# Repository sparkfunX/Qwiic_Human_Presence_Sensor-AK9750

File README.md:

Qwiic Human Presence Sensor - AK9750
========================================

[*SPX-14289*](https://www.sparkfun.com/products/14289)

The AK9750 is a passive infrared sensor with four discrete sensors built into one digital package. PIRs are most often used in security systems to detect the movement of a human talking through the room. If you've ever seen a 1" white sphere in the corner of a room, that's a PIR. We sell a [simple PIR](https://www.sparkfun.com/products/13285) as well. The problem with PIRs is many fold. The vast majority of PIRs use a simple on/off interface. The AK9750 is a digital sensor giving you a 16-bit digital value over I<sup>2</sup>C. Furthermore, the AK9750 has *four* sensors built in! This allows you to detect not only presence but relative distance and direction of movement (for example: PIR2 went off then PIR4 went off so the human is moving left to right).

Each of the four sensors outputs the IR current in pico-amps (-14,286 to 14,286pA). A PIR reading can vary from roughly -200 (no human present) to 1500 when a human is detected standing in front of a given channel but it varies due to environmental factors and other heat sources in view. We've written a library to control the sensor and included a examples showing how to output the sensor readings. We've also written a Processing sketch to visualize the IR sensor readings in real time. 

The Qwiic Human Presence Sensor - AK9750 is rear mounted through the 0.8mm thick PCB. Additionally, the sensor ships without a lens. We've found the sensor to perform quite well and detect human movement over 10 feet (3 meters) away without the standard Fresnel lens. 

Need many eyes in the sky? The ADR jumpers allow up to 3 sensors on a bus. Need more? Our [Qwiic Mux](https://www.sparkfun.com/products/14257) will enable up to 192 sensors for a total of 768 presence readings. Eeek!

This board includes Qwiic connectors. The [Qwiic system](http://www.sparkfun.com/qwiic) enables fast and solderless connection between popular platforms and various sensors and actuators. You can read more about the Qwiic system [here](http://www.sparkfun.com/qwiic).

Repository Contents
-------------------

* **/Documents** - AK9750 datasheet and graph of movement detection. 
* **/Firmware** - Example sketches for the library (.ino). Run these from the Arduino IDE. 
* **/Hardware** - Source files for the PCB layout in EAGLE (.brd, .sch).
* **/Visualizer** - Processing sketch with matching Arduino sketch to see data on a heat map.

License Information
-------------------

This product is _**open source**_!

Please review the LICENSE.md file for license information.

If you have any questions or concerns on licensing, please contact techsupport@sparkfun.com.

Distributed as-is; no warranty is given.

- Your friends at SparkFun.

_<COLLABORATION CREDIT>_

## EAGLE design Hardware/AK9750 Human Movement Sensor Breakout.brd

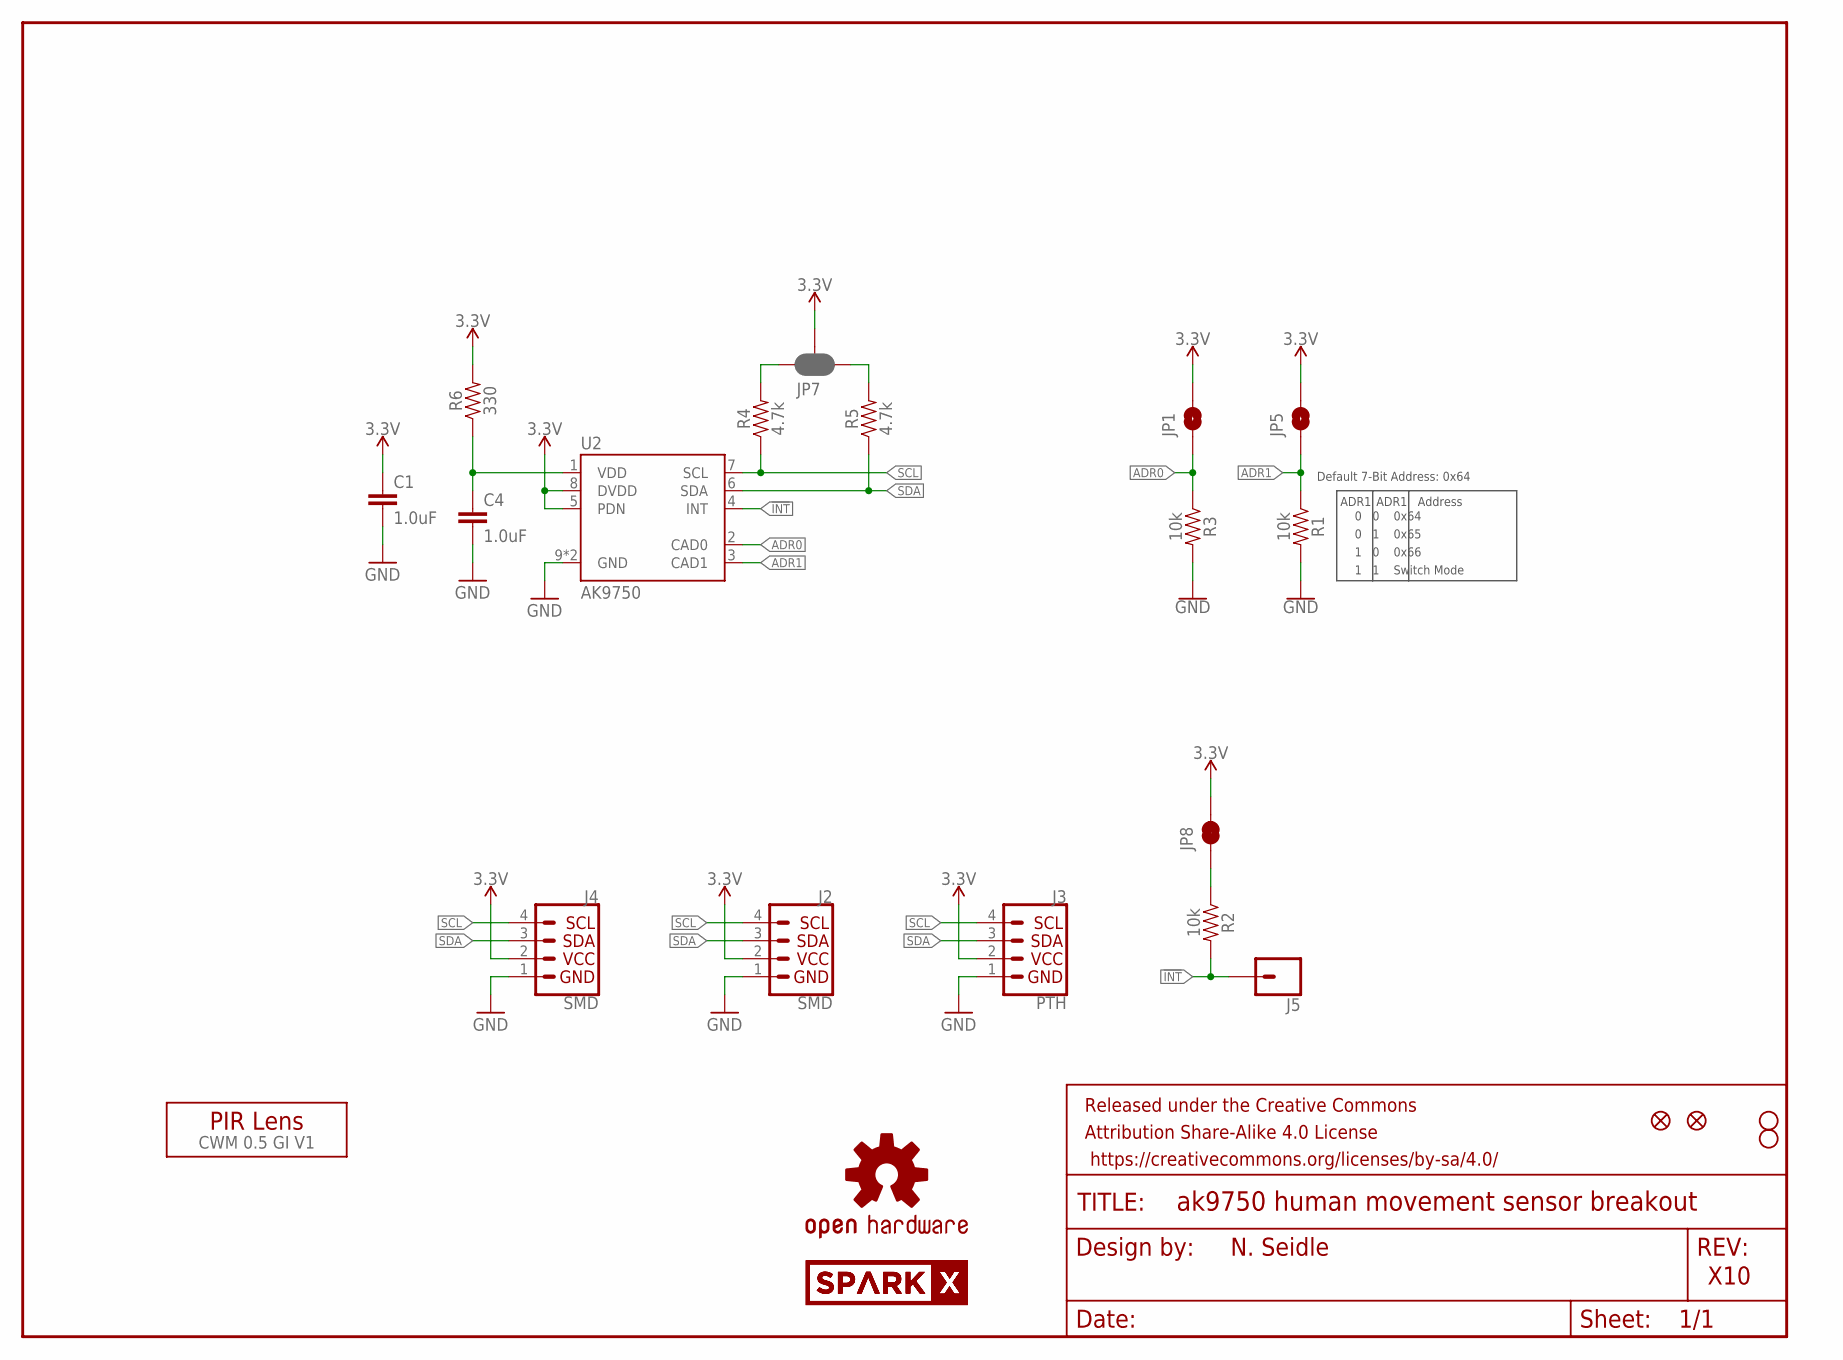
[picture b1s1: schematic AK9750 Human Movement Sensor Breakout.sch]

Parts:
C1, C4: 1.0uF; 0603
FRAME1: FRAME-LETTER; CREATIVE_COMMONS
J2, J4: SMD; 1X04_1MM_RA
J3: PTH; 1X04_NO_SILK
J5: CONN_01PTH_NO_SILK_YES_STOP; 1X01_NO_SILK
JP1, JP5: JUMPER-SMT_2_NO_SILK; SMT-JUMPER_2_NO_SILK
JP2, JP6: FIDUCIALUFIDUCIAL; MICRO-FIDUCIAL
JP3, JP4: STAND-OFF
JP7: JUMPER-SMT_3_2-NC_PASTE_SILK; SMT-JUMPER_3_2-NC_PASTE_SILK
JP8: JUMPER-SMT_2_NC_TRACE_SILK; SMT-JUMPER_2_NC_TRACE_SILK
LOGO1: OSHW-LOGOMINI; OSHW-LOGO-MINI
R1, R2, R3: 10k; 0603
R4, R5: 4.7k; 0603
R6: 330; 0603
U2: AK9750; SON10
U$1, U$2: SPARKX-LOGO4; SPARKX-MEDIUM
U$3: CWM 0.5 GI V1; LENS-CWM-0.5-GI-V1

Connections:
3.3V: C1.1, J2.2 (VCC), J3.2 (VCC), J4.2 (VCC), JP1.2, JP5.2, JP7.2, JP8.2, R6.2, U2.5 (PDN), U2.8 (DVDD)
!INT: J5.1, R2.2, U2.4 (INT)
ADR0: JP1.1, R3.1, U2.2 (CAD0)
ADR1: JP5.1, R1.1, U2.3 (CAD1)
GND: C1.2, C4.2, J2.1 (GND), J3.1 (GND), J4.1 (GND), R1.2, R3.2, U2.9 (GND), U2.10 (GND)
unnamed: JP7.1, R5.2
unnamed: JP7.3, R4.2
unnamed: JP8.1, R2.1
SCL: J2.4 (SCL), J3.4 (SCL), J4.4 (SCL), R4.1, U2.7 (SCL)
SDA: J2.3 (SDA), J3.3 (SDA), J4.3 (SDA), R5.1, U2.6 (SDA)
VDD: C4.1, R6.1, U2.1 (VDD)

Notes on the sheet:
N. Seidle
X10
Default 7-Bit Address: 0x64
ADR1
0 0 0x64
Address
0 1 0x65
1 0 0x66
1 1 Switch Mode

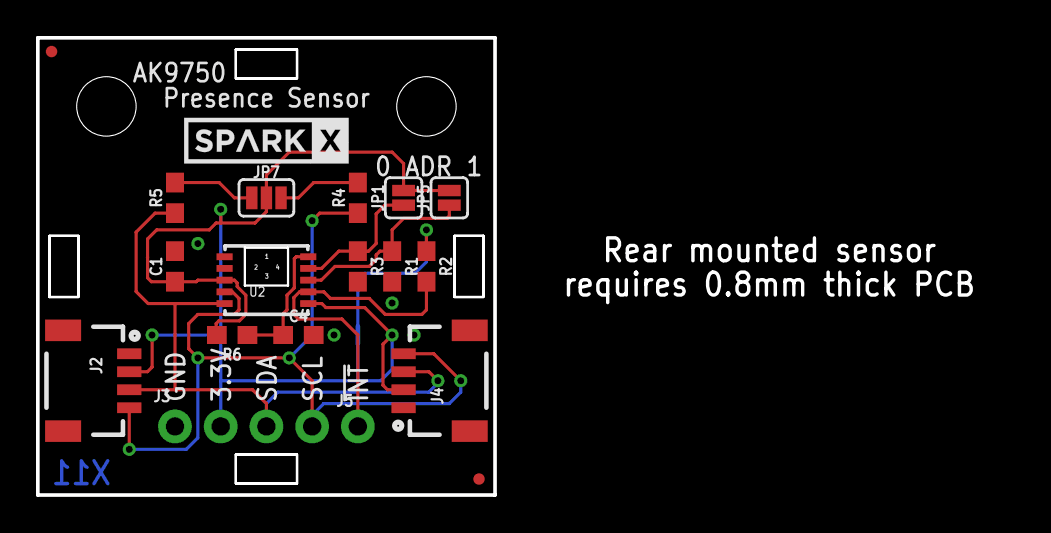
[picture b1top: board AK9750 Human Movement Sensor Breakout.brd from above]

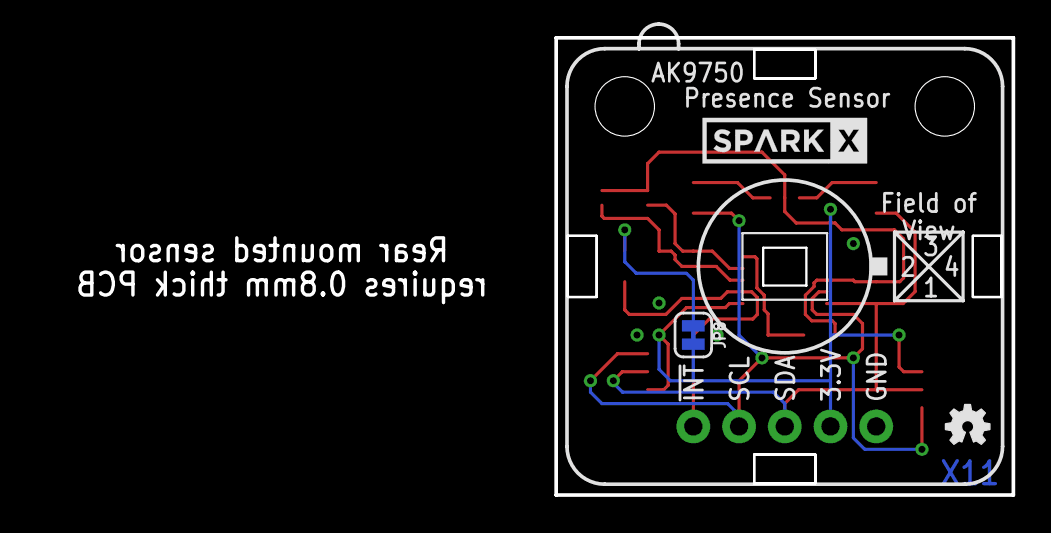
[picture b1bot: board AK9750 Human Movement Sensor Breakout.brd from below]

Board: 2 copper layers, 54.2 x 25.4 mm, 26 parts (4 on the bottom side), 11 nets.

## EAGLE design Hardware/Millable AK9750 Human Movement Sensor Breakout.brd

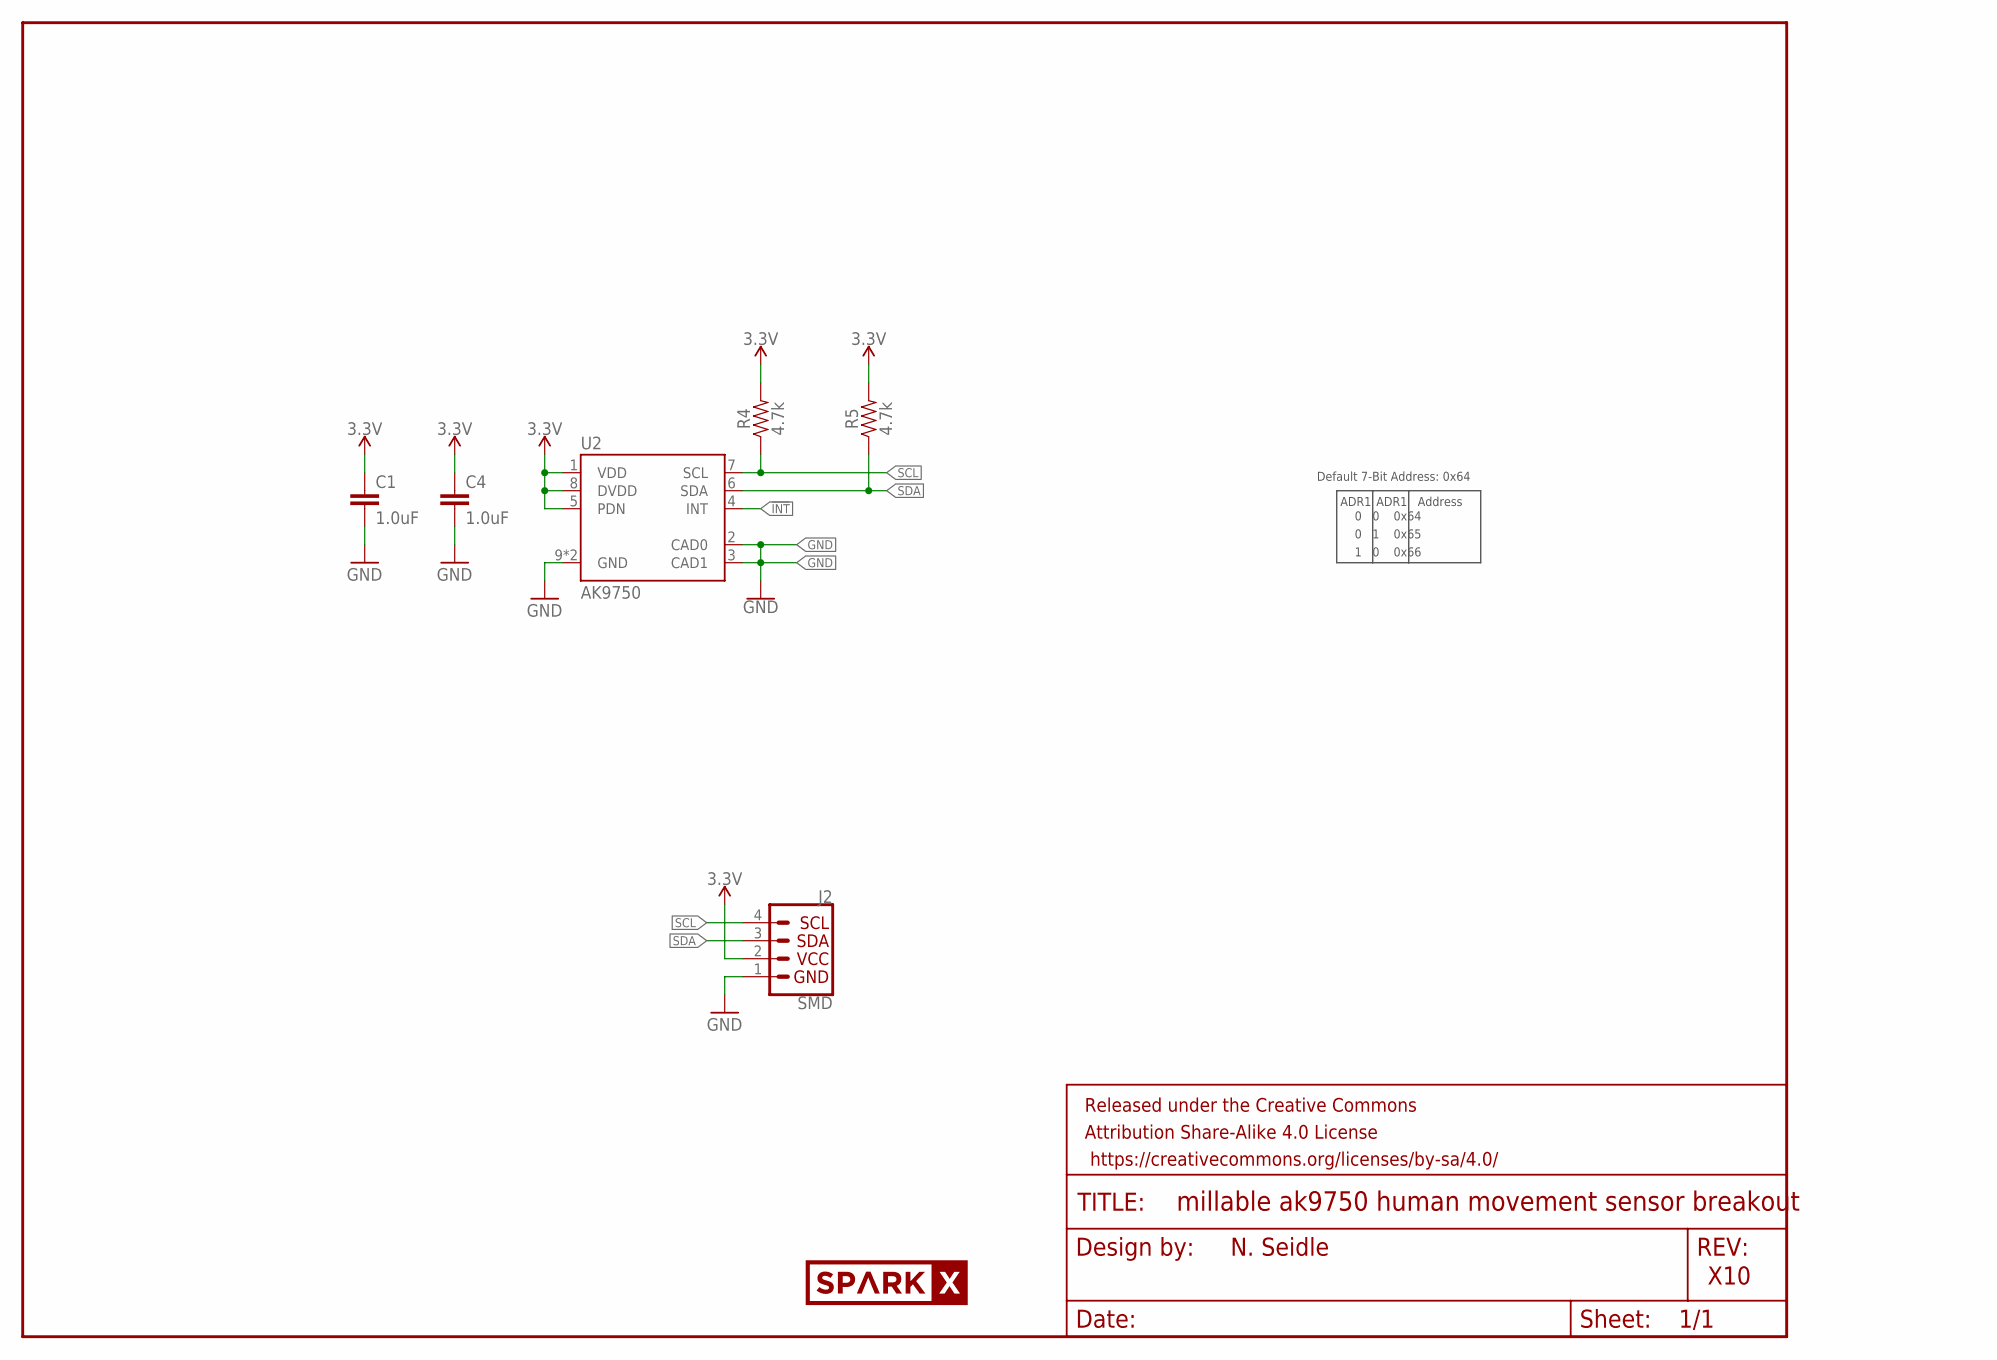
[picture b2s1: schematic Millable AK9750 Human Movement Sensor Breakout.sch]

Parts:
C1, C4: 1.0uF; 0603
FRAME1: FRAME-LETTER; CREATIVE_COMMONS
J2: SMD; 1X04_1MM_RA
R4, R5: 4.7k; 0603
U2: AK9750; SON10
U$2: SPARKX-LOGO4; SPARKX-MEDIUM

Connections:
3.3V: C1.1, C4.1, J2.2 (VCC), R4.2, R5.2, U2.1 (VDD), U2.5 (PDN), U2.8 (DVDD)
!INT: U2.4 (INT)
GND: C1.2, C4.2, J2.1 (GND), U2.2 (CAD0), U2.3 (CAD1), U2.9 (GND), U2.10 (GND)
SCL: J2.4 (SCL), R4.1, U2.7 (SCL)
SDA: J2.3 (SDA), R5.1, U2.6 (SDA)

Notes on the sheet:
N. Seidle
X10
Default 7-Bit Address: 0x64
ADR1
0 0 0x64
Address
0 1 0x65
1 0 0x66

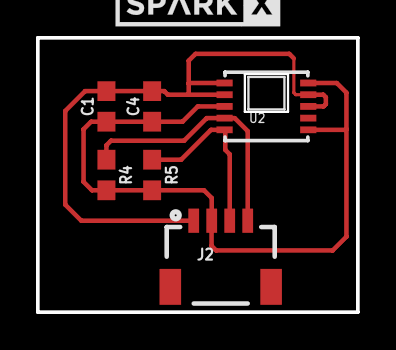
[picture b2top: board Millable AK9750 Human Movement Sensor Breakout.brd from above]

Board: 2 copper layers, 17.8 x 15.2 mm, 8 parts (0 on the bottom side), 4 nets.

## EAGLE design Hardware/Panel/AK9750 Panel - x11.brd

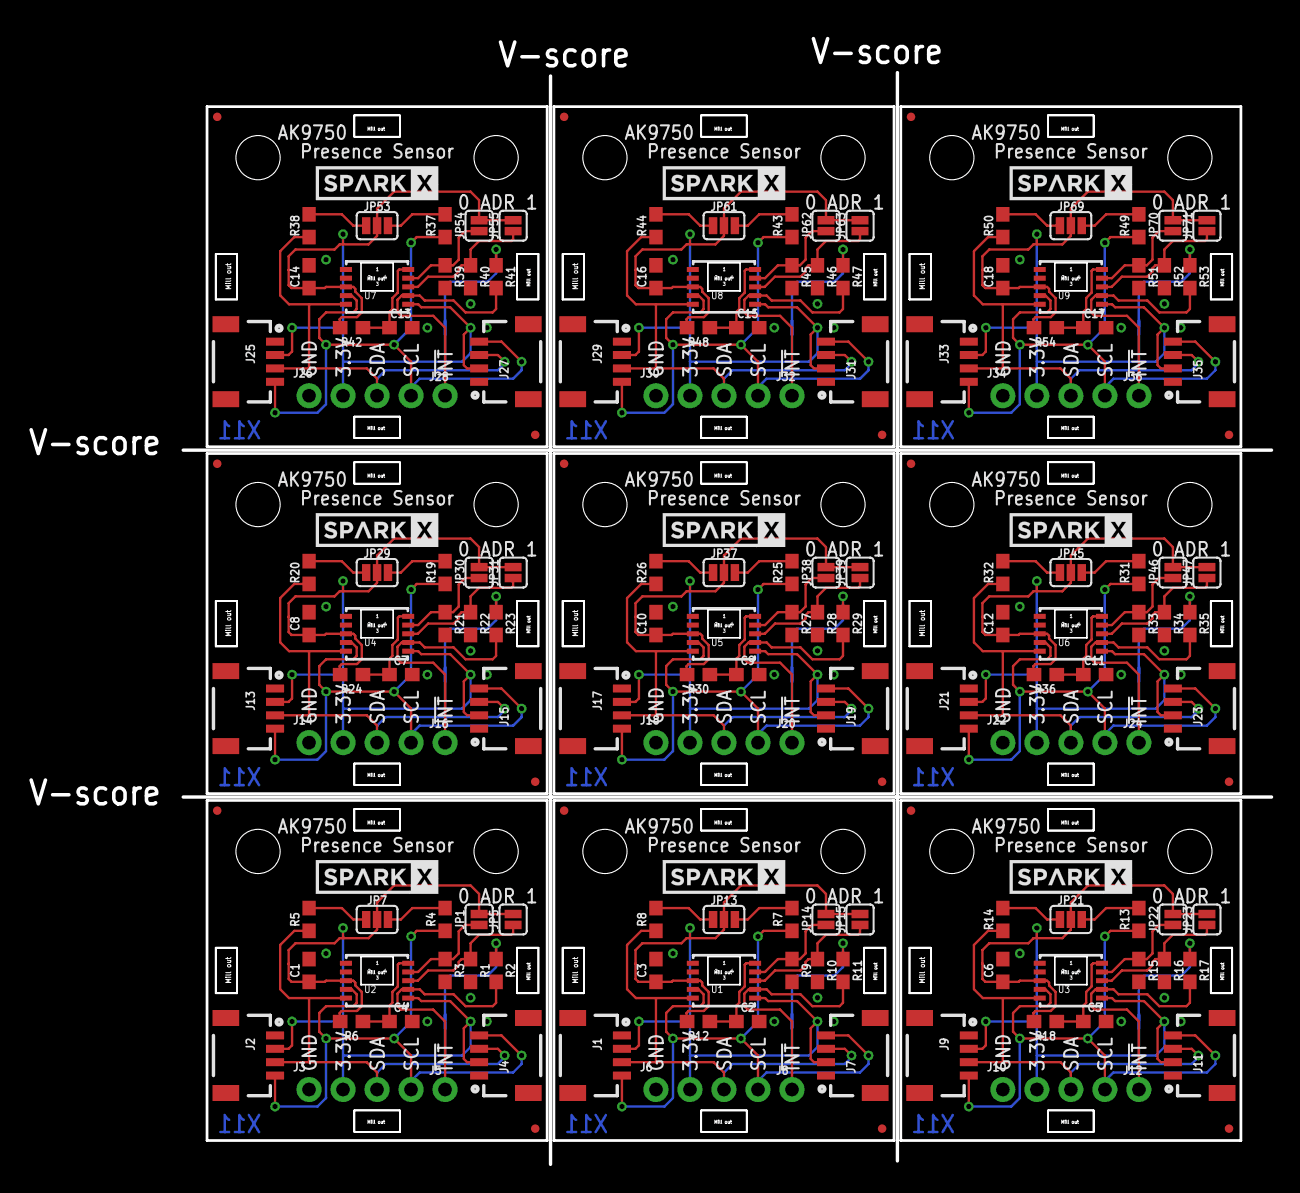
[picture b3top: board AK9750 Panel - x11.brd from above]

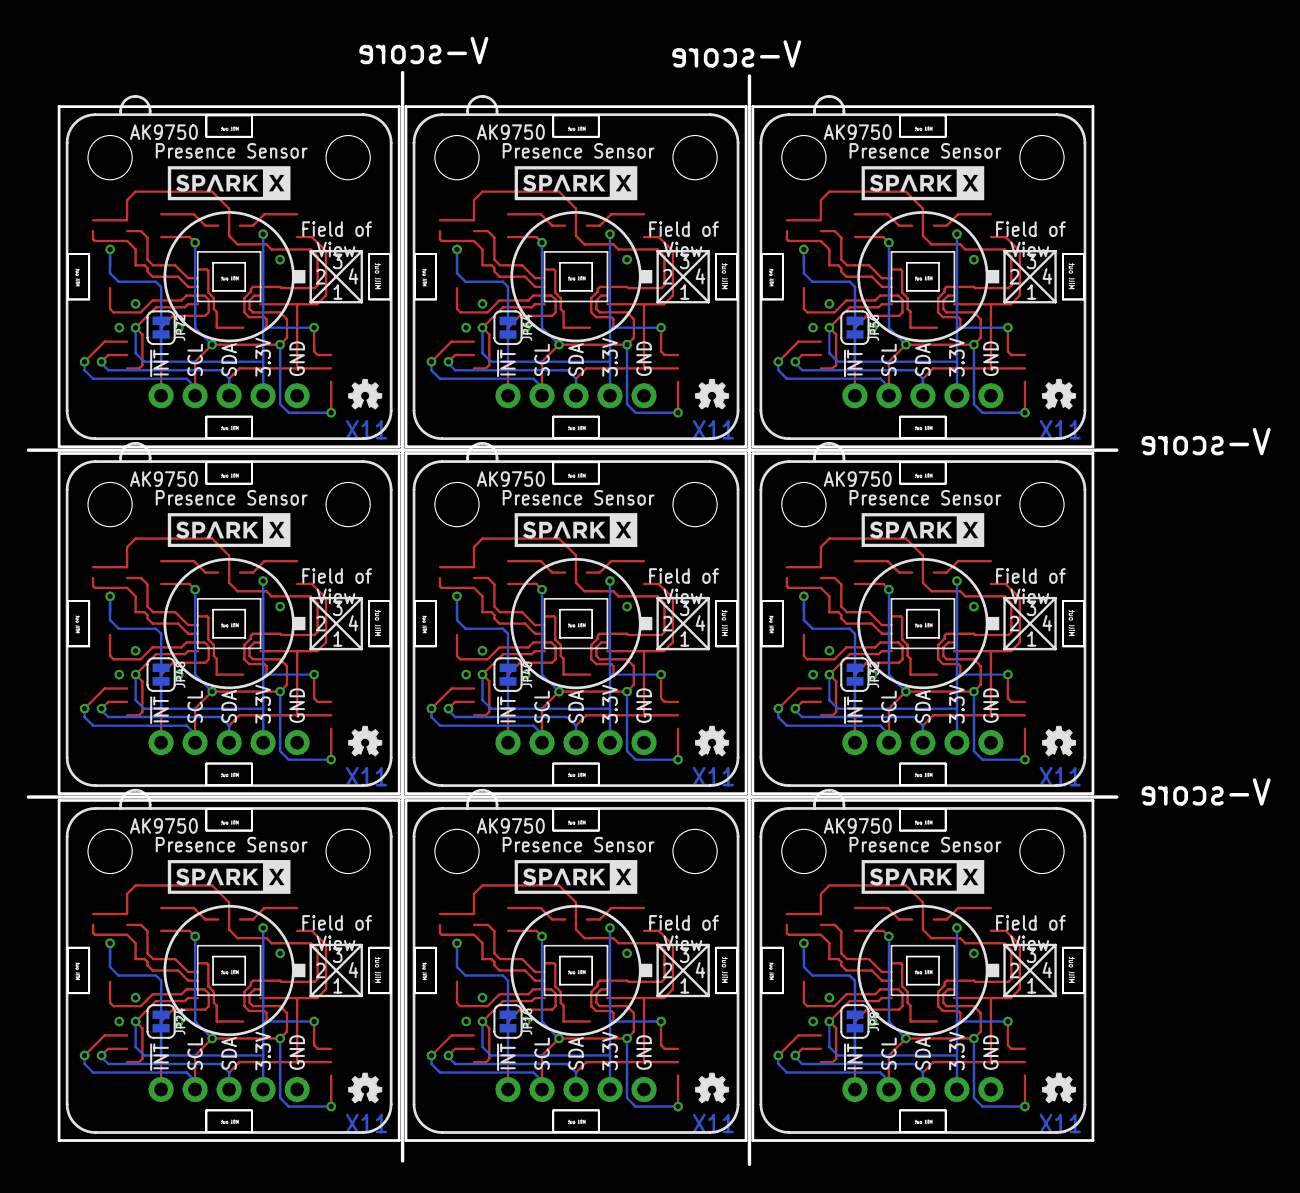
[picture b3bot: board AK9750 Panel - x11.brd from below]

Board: 2 copper layers, 92.8 x 84.8 mm, 225 parts (36 on the bottom side), 99 nets.

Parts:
C1, C2, C3, C4, C5, C6, C7, C8, C9, C10, C11, C12, C13, C14, C15, C16, C17, C18: 1.0uF; 0603
J1, J2, J4, J7, J9, J11, J13, J15, J17, J19, J21, J23, J25, J27, J29, J31, J33, J35: SMD; 1X04_1MM_RA
J3, J6, J10, J14, J18, J22, J26, J30, J34: PTH; 1X04_NO_SILK
J5, J8, J12, J16, J20, J24, J28, J32, J36: 1X01_NO_SILK
JP1, JP5, JP14, JP15, JP22, JP23, JP30, JP31, JP38, JP39, JP46, JP47, JP54, JP55, JP62, JP63, JP70, JP71: SMT-JUMPER_2_NO_SILK
JP2, JP6, JP11, JP12, JP19, JP20, JP27, JP28, JP35, JP36, JP43, JP44, JP51, JP52, JP59, JP60, JP67, JP68: FIDUCIALUFIDUCIAL; MICRO-FIDUCIAL
JP3, JP4, JP9, JP10, JP17, JP18, JP25, JP26, JP33, JP34, JP41, JP42, JP49, JP50, JP57, JP58, JP65, JP66: STAND-OFF
JP7, JP13, JP21, JP29, JP37, JP45, JP53, JP61, JP69: SMT-JUMPER_3_2-NC_PASTE_SILK
JP8, JP16, JP24, JP32, JP40, JP48, JP56, JP64, JP72: SMT-JUMPER_2_NC_TRACE_SILK
LOGO1, LOGO2, LOGO3, LOGO4, LOGO5, LOGO6, LOGO7, LOGO8, LOGO9: OSHW-LOGOMINI; OSHW-LOGO-MINI
R1, R2, R3, R9, R10, R11, R15, R16, R17, R21, R22, R23, R27, R28, R29, R33, R34, R35, R39, R40, R41, R45, R46, R47, R51, R52, R53: 10k; 0603
R4, R5, R7, R8, R13, R14, R19, R20, R25, R26, R31, R32, R37, R38, R43, R44, R49, R50: 4.7k; 0603
R6, R12, R18, R24, R30, R36, R42, R48, R54: 330; 0603
U1, U2, U3, U4, U5, U6, U7, U8, U9: AK9750; SON10
U$1, U$2, U$4, U$5, U$7, U$8, U$10, U$11, U$13, U$14, U$16, U$17, U$19, U$20, U$22, U$23, U$25, U$26: SPARKX-LOGO4; SPARKX-MEDIUM
U$3, U$6, U$9, U$12, U$15, U$18, U$21, U$24, U$27: CWM 0.5 GI V1; LENS-CWM-0.5-GI-V1

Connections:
3.3V: C1.1, J2.2, J3.2, J4.2, JP1.2, JP5.2, JP7.2, JP8.2, R6.2, U2.5, U2.8
3.3V1: C3.1, J1.2, J6.2, J7.2, JP13.2, JP14.2, JP15.2, JP16.2, R12.2, U1.5, U1.8
3.3V2: C6.1, J9.2, J10.2, J11.2, JP21.2, JP22.2, JP23.2, JP24.2, R18.2, U3.5, U3.8
3.3V3: C8.1, J13.2, J14.2, J15.2, JP29.2, JP30.2, JP31.2, JP32.2, R24.2, U4.5, U4.8
3.3V4: C10.1, J17.2, J18.2, J19.2, JP37.2, JP38.2, JP39.2, JP40.2, R30.2, U5.5, U5.8
3.3V5: C12.1, J21.2, J22.2, J23.2, JP45.2, JP46.2, JP47.2, JP48.2, R36.2, U6.5, U6.8
3.3V6: C14.1, J25.2, J26.2, J27.2, JP53.2, JP54.2, JP55.2, JP56.2, R42.2, U7.5, U7.8
3.3V7: C16.1, J29.2, J30.2, J31.2, JP61.2, JP62.2, JP63.2, JP64.2, R48.2, U8.5, U8.8
3.3V8: C18.1, J33.2, J34.2, J35.2, JP69.2, JP70.2, JP71.2, JP72.2, R54.2, U9.5, U9.8
!INT: J5.1, R2.2, U2.4
!INT1: J8.1, R11.2, U1.4
!INT2: J12.1, R17.2, U3.4
!INT3: J16.1, R23.2, U4.4
!INT4: J20.1, R29.2, U5.4
!INT5: J24.1, R35.2, U6.4
!INT6: J28.1, R41.2, U7.4
!INT7: J32.1, R47.2, U8.4
!INT8: J36.1, R53.2, U9.4
ADR0: JP1.1, R3.1, U2.2
ADR1: JP5.1, R1.1, U2.3
ADR2: JP14.1, R9.1, U1.2
ADR3: JP15.1, R10.1, U1.3
ADR4: JP22.1, R15.1, U3.2
ADR5: JP23.1, R16.1, U3.3
ADR6: JP30.1, R21.1, U4.2
ADR7: JP31.1, R22.1, U4.3
ADR8: JP38.1, R27.1, U5.2
ADR9: JP39.1, R28.1, U5.3
ADR10: JP46.1, R33.1, U6.2
ADR11: JP47.1, R34.1, U6.3
ADR12: JP54.1, R39.1, U7.2
ADR13: JP55.1, R40.1, U7.3
ADR14: JP62.1, R45.1, U8.2
ADR15: JP63.1, R46.1, U8.3
ADR16: JP70.1, R51.1, U9.2
ADR17: JP71.1, R52.1, U9.3
GND9: C1.2, C4.2, J2.1, J3.1, J4.1, R1.2, R3.2, U2.9, U2.10
GND10: C2.2, C3.2, J1.1, J6.1, J7.1, R9.2, R10.2, U1.9, U1.10
GND11: C5.2, C6.2, J9.1, J10.1, J11.1, R15.2, R16.2, U3.9, U3.10
GND12: C7.2, C8.2, J13.1, J14.1, J15.1, R21.2, R22.2, U4.9, U4.10
GND13: C9.2, C10.2, J17.1, J18.1, J19.1, R27.2, R28.2, U5.9, U5.10
GND14: C11.2, C12.2, J21.1, J22.1, J23.1, R33.2, R34.2, U6.9, U6.10
GND15: C13.2, C14.2, J25.1, J26.1, J27.1, R39.2, R40.2, U7.9, U7.10
GND16: C15.2, C16.2, J29.1, J30.1, J31.1, R45.2, R46.2, U8.9, U8.10
GND17: C17.2, C18.2, J33.1, J34.1, J35.1, R51.2, R52.2, U9.9, U9.10
unnamed: JP7.1, R5.2
unnamed: JP7.3, R4.2
unnamed: JP8.1, R2.1
unnamed: JP13.1, R8.2
unnamed: JP13.3, R7.2
unnamed: JP16.1, R11.1
unnamed: JP21.1, R14.2
unnamed: JP21.3, R13.2
unnamed: JP24.1, R17.1
unnamed: JP29.1, R20.2
unnamed: JP29.3, R19.2
unnamed: JP32.1, R23.1
unnamed: JP37.1, R26.2
unnamed: JP37.3, R25.2
unnamed: JP40.1, R29.1
unnamed: JP45.1, R32.2
unnamed: JP45.3, R31.2
unnamed: JP48.1, R35.1
unnamed: JP53.1, R38.2
unnamed: JP53.3, R37.2
unnamed: JP56.1, R41.1
unnamed: JP61.1, R44.2
unnamed: JP61.3, R43.2
unnamed: JP64.1, R47.1
unnamed: JP69.1, R50.2
unnamed: JP69.3, R49.2
unnamed: JP72.1, R53.1
SCL: J2.4, J3.4, J4.4, R4.1, U2.7
SCL1: J1.4, J6.4, J7.4, R7.1, U1.7
SCL2: J9.4, J10.4, J11.4, R13.1, U3.7
SCL3: J13.4, J14.4, J15.4, R19.1, U4.7
SCL4: J17.4, J18.4, J19.4, R25.1, U5.7
SCL5: J21.4, J22.4, J23.4, R31.1, U6.7
SCL6: J25.4, J26.4, J27.4, R37.1, U7.7
SCL7: J29.4, J30.4, J31.4, R43.1, U8.7
SCL8: J33.4, J34.4, J35.4, R49.1, U9.7
SDA: J2.3, J3.3, J4.3, R5.1, U2.6
SDA1: J1.3, J6.3, J7.3, R8.1, U1.6
SDA2: J9.3, J10.3, J11.3, R14.1, U3.6
SDA3: J13.3, J14.3, J15.3, R20.1, U4.6
SDA4: J17.3, J18.3, J19.3, R26.1, U5.6
SDA5: J21.3, J22.3, J23.3, R32.1, U6.6
SDA6: J25.3, J26.3, J27.3, R38.1, U7.6
SDA7: J29.3, J30.3, J31.3, R44.1, U8.6
SDA8: J33.3, J34.3, J35.3, R50.1, U9.6
VDD: C4.1, R6.1, U2.1
VDD1: C2.1, R12.1, U1.1
VDD2: C5.1, R18.1, U3.1
VDD3: C7.1, R24.1, U4.1
VDD4: C9.1, R30.1, U5.1
VDD5: C11.1, R36.1, U6.1
VDD6: C13.1, R42.1, U7.1
VDD7: C15.1, R48.1, U8.1
VDD8: C17.1, R54.1, U9.1

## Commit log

2017-04-09 :neckbeard: Added .gitattributes & .gitignore files
2017-04-09 Added lens FP. Increased aperature for IR sensor.
2017-04-17 Adding example sketches
2017-04-17 Adding panel files
2017-04-19 Firming up examples
2017-04-24 Adding processing heat mapper example
2017-04-25 Adding readmes and visualizer.
2017-04-25 Removing extra files

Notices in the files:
parts and their libraries:
SparkFun-Resistors: Licensing: Creative Commons ShareAlike 4.0 International - https://creativecommons.org/licenses/by-sa/4.0
SparkFun-Aesthetics: Released under the Creative Commons Attribution Share-Alike 4.0 License
SparkFun-Aesthetics: https://creativecommons.org/licenses/by-sa/4.0
